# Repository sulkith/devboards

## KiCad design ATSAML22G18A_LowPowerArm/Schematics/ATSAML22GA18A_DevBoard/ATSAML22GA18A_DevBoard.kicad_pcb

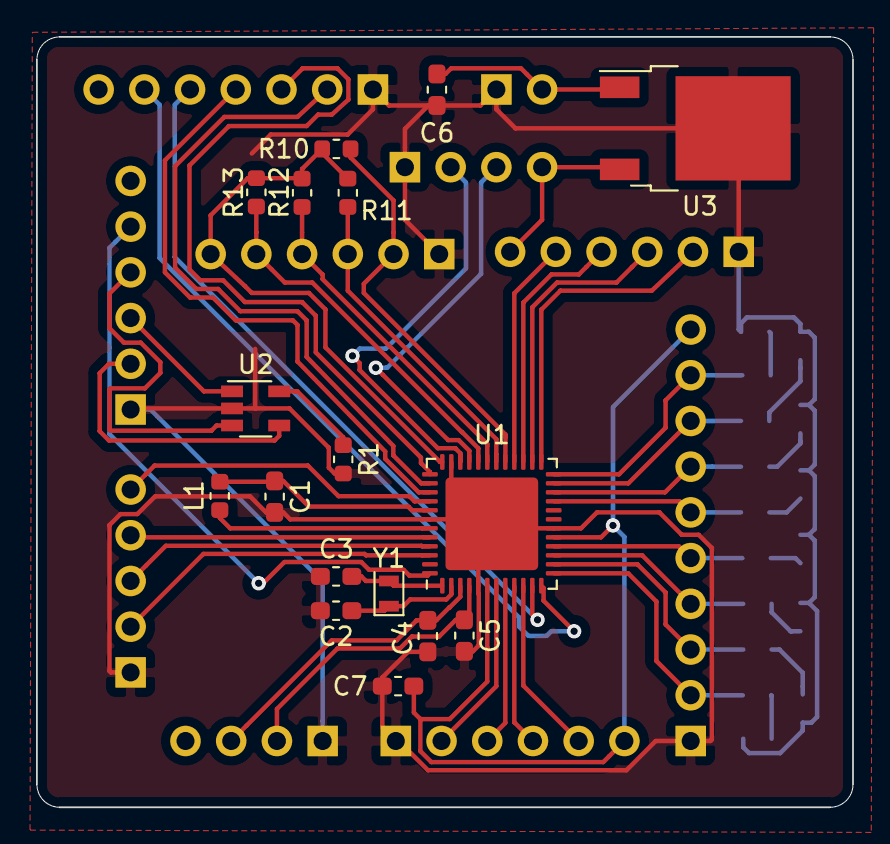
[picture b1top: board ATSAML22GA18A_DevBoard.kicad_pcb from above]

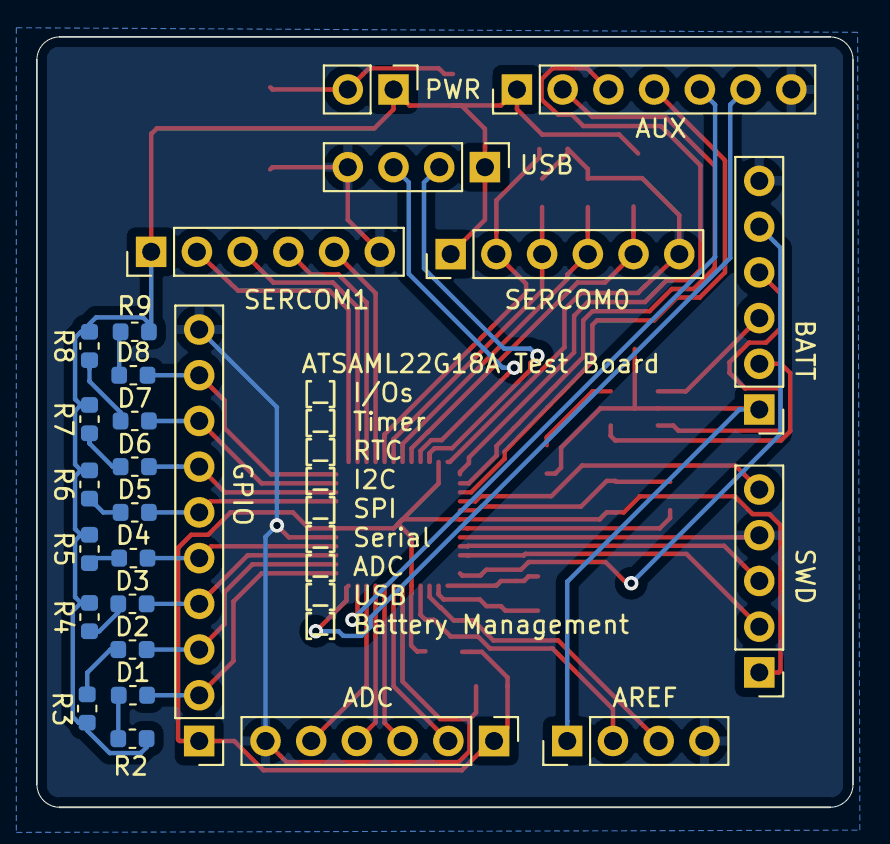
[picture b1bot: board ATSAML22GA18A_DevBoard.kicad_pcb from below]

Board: 2 copper layers, 45.3 x 42.8 mm, 43 parts (26 on the bottom side), 52 nets.

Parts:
ADC: Conn_01x06_Female; PinHeader_1x06_P2.54mm_Vertical
AREF: Conn_01x04_Female; PinHeader_1x04_P2.54mm_Vertical
AUX: Conn_01x07_Female; PinHeader_1x07_P2.54mm_Vertical
BATT: Conn_01x06_Female; PinHeader_1x06_P2.54mm_Vertical
C1: 100nF; C_0603_1608Metric_Pad1.05x0.95mm_HandSolder
C2, C3, C4, C5, C6, C7: C; C_0603_1608Metric_Pad1.05x0.95mm_HandSolder
D1, D2, D3, D4, D5, D6, D7, D8: LED; R_0603_1608Metric
GPIO: Conn_01x10_Female; PinHeader_1x10_P2.54mm_Vertical
L1: 10µH; L_0603_1608Metric
PWR: Conn_01x02_Female; PinHeader_1x02_P2.54mm_Vertical
R1: 10k; R_0603_1608Metric
R2, R3, R4, R5, R6, R7, R8, R9, R10, R11, R12, R13: R; R_0603_1608Metric
SERCOM0, SERCOM1: Conn_01x06_Female; PinHeader_1x06_P2.54mm_Vertical
SWD: Conn_01x05_Female; PinHeader_1x05_P2.54mm_Vertical
U1: ATSAML21G18B-MUT; QFN-48-1EP_7x7mm_P0.5mm_EP5.15x5.15mm
U2: LTC4054ES5-4.2; TSOT-23-5
U3: LF33_TO252; TO-252-2
USB: Conn_01x04_Female; PinHeader_1x04_P2.54mm_Vertical
Y1: Crystal; Crystal_SMD_2012-2Pin_2.0x1.2mm

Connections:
AIN2_NMI: ADC.2, U1.7
AIN3: ADC.3, U1.8
AIN4: ADC.4, U1.9
AIN5: ADC.5, U1.10
BAT+: BATT.4, U2.3
CHG_IN: BATT.2, U2.4
CHG_STAT: BATT.3, U2.1
EXTINT6: AUX.5, U1.11
EXTINT7: AUX.6, U1.12
GCLK_IO: AUX.4, U1.39
GND: ADC.1, AREF.1, AUX.1, BATT.1, C1.2, C2.2, C3.2, C4.2, C5.2, C6.2, C7.2, GPIO.1, PWR.1, R1.2, R2.2, R3.2, R4.2, R5.2, R6.2, R7.2, R8.2, R9.2, SERCOM0.1, SERCOM1.1, SWD.1, U1.5, U1.18, U1.35, U1.42, U1.49, U2.2, U3.2, USB.1
GPIO0: D1.2, GPIO.2, U1.13
GPIO1: D2.2, GPIO.3, U1.14
GPIO2: D3.2, GPIO.4, U1.15
GPIO3: D4.2, GPIO.5, U1.16
GPIO4: D5.2, GPIO.6, U1.21
GPIO5: D6.2, GPIO.7, U1.22
GPIO6: D7.2, GPIO.8, U1.23
GPIO7: D8.2, GPIO.9, U1.24
unnamed: C6.1, PWR.2, U3.1
unnamed: D1.1, R2.1
unnamed: D2.1, R3.1
unnamed: D3.1, R4.1
unnamed: D4.1, R5.1
unnamed: D5.1, R6.1
unnamed: D6.1, R7.1
unnamed: D7.1, R8.1
unnamed: D8.1, R9.1
unnamed: R1.1, U2.5
RESET: SWD.5, U1.40
SERCOM0_0: R10.1, SERCOM0.2, U1.29
SERCOM0_1: R11.1, SERCOM0.3, U1.30
SERCOM0_2: R12.1, SERCOM0.4, U1.31
SERCOM0_2_a1__XIN__USB_SOF: AUX.3, U1.37
SERCOM0_3: R13.1, SERCOM0.5, U1.32
SERCOM0_3_a1__XOUT: AUX.2, U1.38
SERCOM1_0: SERCOM1.2, U1.25
SERCOM1_1: SERCOM1.3, U1.26
SERCOM1_2: SERCOM1.4, U1.27
SERCOM1_3: SERCOM1.5, U1.28
SWCLK: SWD.3, U1.45
SWDIO: SWD.2, U1.46
USB_D+: U1.33, USB.3
USB_D-: U1.34, USB.2
VBAT: BATT.5, U1.48
VCC: ADC.6, AREF.4, AUX.7, BATT.6, C7.1, GPIO.10, R10.2, R11.2, R12.2, R13.2, SERCOM0.6, SERCOM1.6, SWD.4, U1.6, U1.17, U1.36, U1.44, U3.3, USB.4
VDDCORE: C1.1, L1.2, U1.41
VDDOUT: L1.1, U1.43
VREFA: AREF.2, C5.1, U1.4
VREFB: AREF.3, C4.1, U1.3
XIN32: C3.1, U1.1, Y1.2
XOUT32: C2.1, U1.2, Y1.1

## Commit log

2020-05-23 added ATSAML22GA18A_DevBoard for a Low Power Atmel Arm Controller
2020-05-23 improved documentation in the schematic
2020-05-24 cleanup of the PCB, and some comments
2020-05-24 added Gerber Files
2020-05-24 added a first compilable test program
2020-05-24 added gitignore
2020-05-24 added size output while generating hex file
2020-05-24 added all sections in the 0x8000 Area to the hex file, hopefully this is correct
2020-06-01 got the Devboards IOs working. Thanks Mick for the great tutorial: https://www.mickmake.com/post/program-atmel-sam-without-ide-tutorial/
2020-06-01 found a better Notation for the Port Access https://community.atmel.com/forum/i2c-communication-samd21g18a and a Link to a i2c example ;-)
2020-06-02 added C++ to the Makefile
2020-06-07 cleanup
2020-06-07 added a importer for Atmel Start Code, so it is easy to replace the includen Base Config
2020-06-07 uncommented the main part
2020-06-11 added a Tesproject for twi SSD1306
2020-06-11 cleanup and added c++ functionality
2020-06-11 got the i2c working
2020-06-11 updated library and filled display
2020-06-21 Added starting and stopping of openocd to the upload and debug command
2020-06-21 updated atstart files
2020-06-21 improved communcation with openocd
2020-06-21 improved Display output
2020-06-21 used th hpl for i2c access, which is a lot faster
2020-06-21 fixed a missing variable name...
2020-07-11 First Steps with the NUCLEO-L053R8 Board
2020-07-12 Added Standby mode with RTC and WKUP_PIN1 Wakeup
